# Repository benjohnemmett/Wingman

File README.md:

# Wingman
Hardware layout and code for a basic fixed wing flight controller.

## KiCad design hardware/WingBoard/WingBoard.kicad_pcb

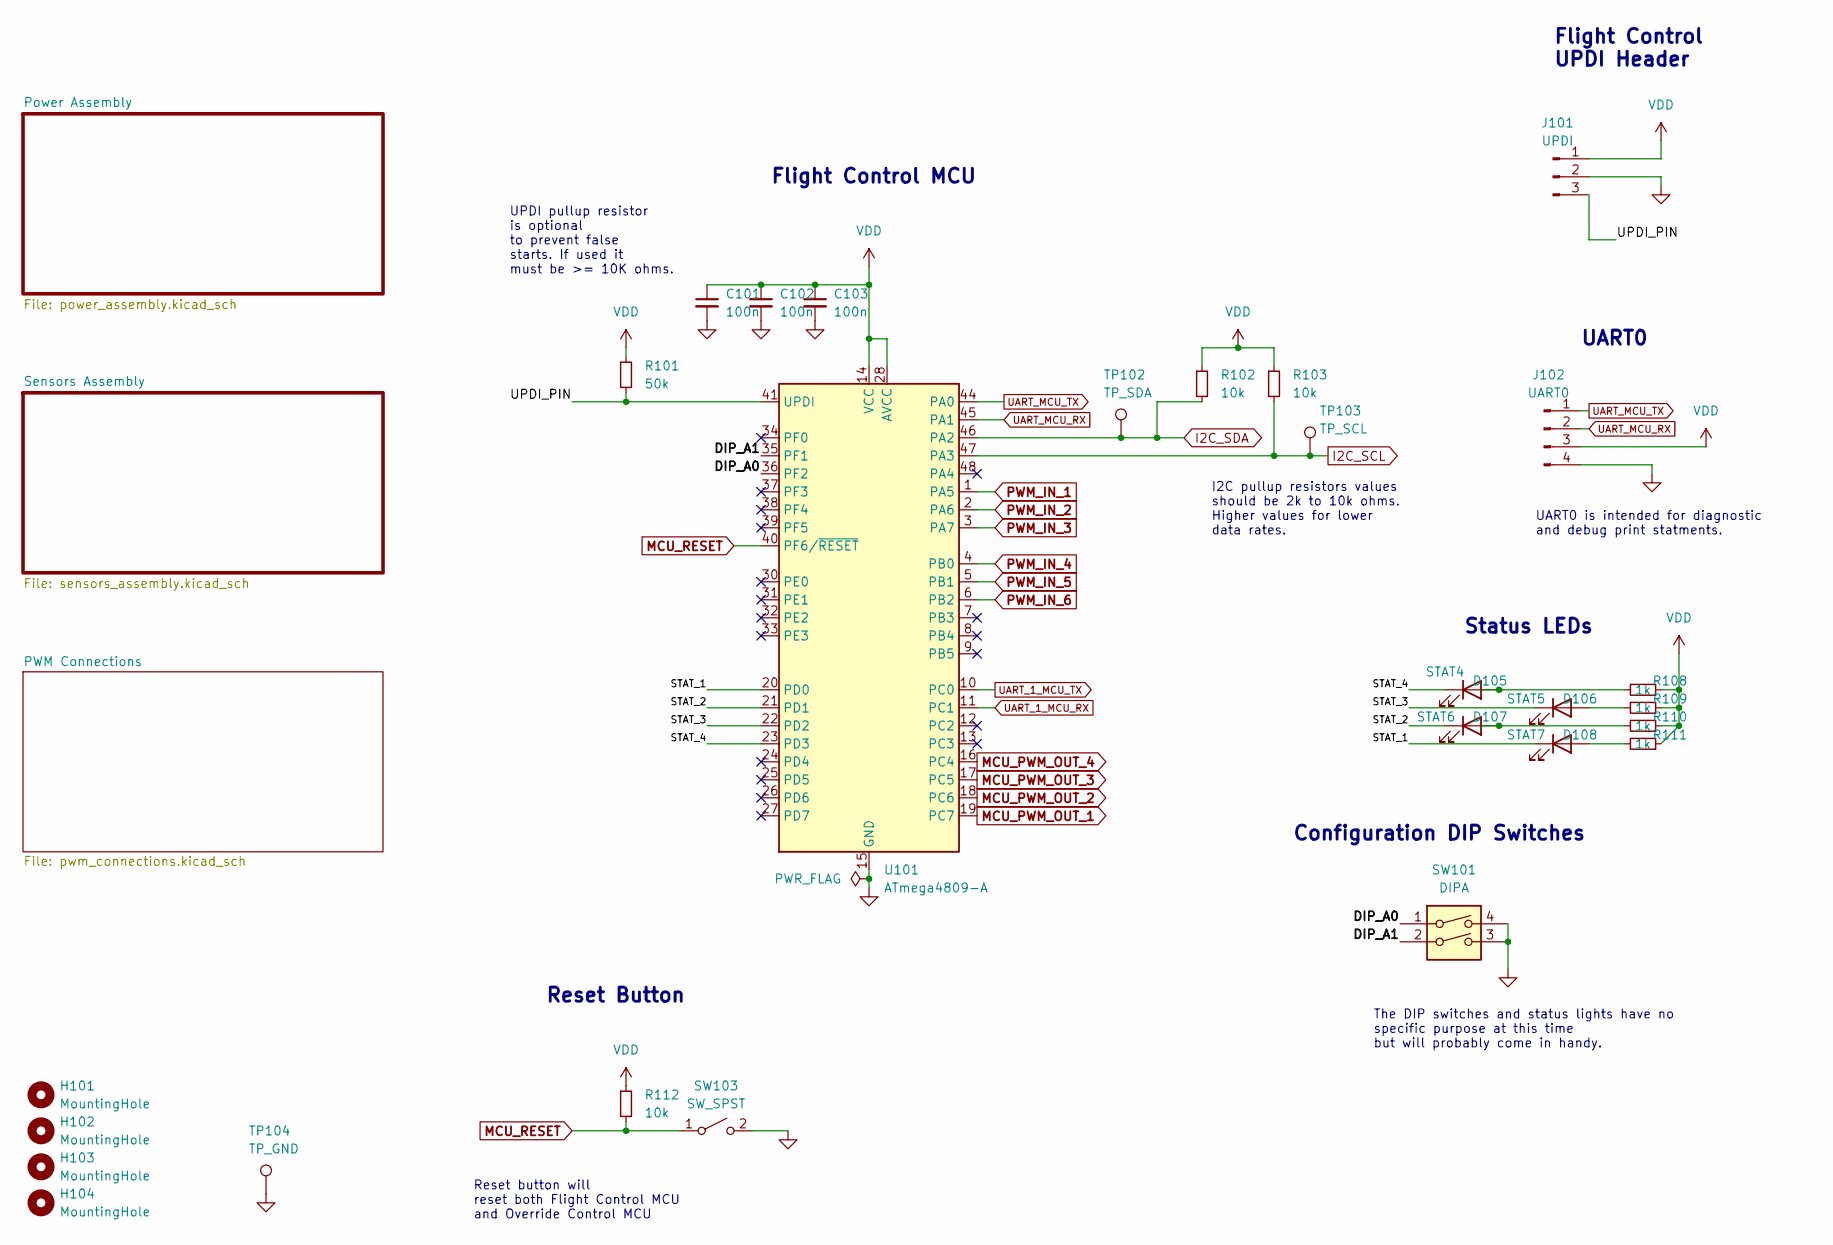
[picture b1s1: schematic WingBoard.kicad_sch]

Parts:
C101, C102, C103: 100n; C_0805_2012Metric_Pad1.18x1.45mm_HandSolder
D105: STAT4; LED_0805_2012Metric_Pad1.15x1.40mm_HandSolder
D106: STAT5; LED_0805_2012Metric_Pad1.15x1.40mm_HandSolder
D107: STAT6; LED_0805_2012Metric_Pad1.15x1.40mm_HandSolder
D108: STAT7; LED_0805_2012Metric_Pad1.15x1.40mm_HandSolder
H101, H102, H103, H104: MountingHole; MountingHole_3mm_Pad_Via
J101: UPDI; PinHeader_1x03_P2.54mm_Vertical
J102: UART0; PinHeader_1x04_P2.54mm_Vertical
R101: 50k; R_0805_2012Metric_Pad1.20x1.40mm_HandSolder
R102, R103, R112: 10k; R_0805_2012Metric_Pad1.20x1.40mm_HandSolder
R108, R109, R110, R111: 1k; R_0805_2012Metric_Pad1.20x1.40mm_HandSolder
SW101: DIPA; SW_DIP_SPSTx02_Slide_Copal_CHS-02B_W7.62mm_P1.27mm
SW103: SW_SPST; R-668127
TP102: TP_SDA; TestPoint_Pad_D1.5mm
TP103: TP_SCL; TestPoint_Pad_D1.5mm
TP104: TP_GND; TestPoint_Pad_D1.5mm
U101: ATmega4809-A; TQFP-48_7x7mm_P0.5mm

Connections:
/DIP_A0: SW101.1, U101.36 (PF2)
/DIP_A1: SW101.2, U101.35 (PF1)
/STAT_1: D108.1 (K), U101.20 (PD0)
/STAT_2: D107.1 (K), U101.21 (PD1)
/STAT_3: D106.1 (K), U101.22 (PD2)
/STAT_4: D105.1 (K), U101.23 (PD3)
/UPDI_PIN: J101.3, R101.2, U101.41 (UPDI)
GND: C101.2, C102.2, C103.2, J101.2, J102.4, SW101.3, SW101.4, SW103.2 (B), TP104.1, U101.15 (GND), U101.29 (GND), U101.43 (GND); also elsewhere on the board
I2C_SCL: R103.2, TP103.1, U101.47 (PA3); also elsewhere on the board
I2C_SDA: R102.2, TP102.1, U101.46 (PA2); also elsewhere on the board
MCU_PWM_OUT_1: U101.19 (PC7); also elsewhere on the board
MCU_PWM_OUT_2: U101.18 (PC6); also elsewhere on the board
MCU_PWM_OUT_3: U101.17 (PC5); also elsewhere on the board
MCU_PWM_OUT_4: U101.16 (PC4); also elsewhere on the board
MCU_RESET: R112.2, SW103.1 (A), U101.40 (PF6/~RESET); also elsewhere on the board
unnamed: D105.2 (A), R108.2
unnamed: D106.2 (A), R109.2
unnamed: D107.2 (A), R110.2
unnamed: D108.2 (A), R111.2
PWM_IN_1: U101.1 (PA5); also elsewhere on the board
PWM_IN_2: U101.2 (PA6); also elsewhere on the board
PWM_IN_3: U101.3 (PA7); also elsewhere on the board
PWM_IN_4: U101.4 (PB0); also elsewhere on the board
PWM_IN_5: U101.5 (PB1); also elsewhere on the board
PWM_IN_6: U101.6 (PB2); also elsewhere on the board
UART_1_MCU_RX: U101.11 (PC1); also elsewhere on the board
UART_1_MCU_TX: U101.10 (PC0); also elsewhere on the board
UART_MCU_RX: J102.2, U101.45 (PA1)
UART_MCU_TX: J102.1, U101.44 (PA0)
VDD: C101.1, C102.1, C103.1, J101.1, J102.3, R101.1, R102.1, R103.1, R108.1, R109.1, R110.1, R111.1, R112.1, U101.14 (VCC), U101.28 (AVCC), U101.42 (VCC); also elsewhere on the board

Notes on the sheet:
Configuration DIP Switches
Reset Button
Flight Control MCU
UPDI pullup resistor is optional to prevent false starts. If used it must be >= 10K ohms.
The DIP switches and status lights have no specific purpose at this time but will probably come in handy.
Reset button will reset both Flight Control MCU and Override Control MCU
Flight Control UPDI Header
Status LEDs
UART0 is intended for diagnostic and debug print statments.
I2C pullup resistors values should be 2k to 10k ohms. Higher values for lower data rates.
UART0

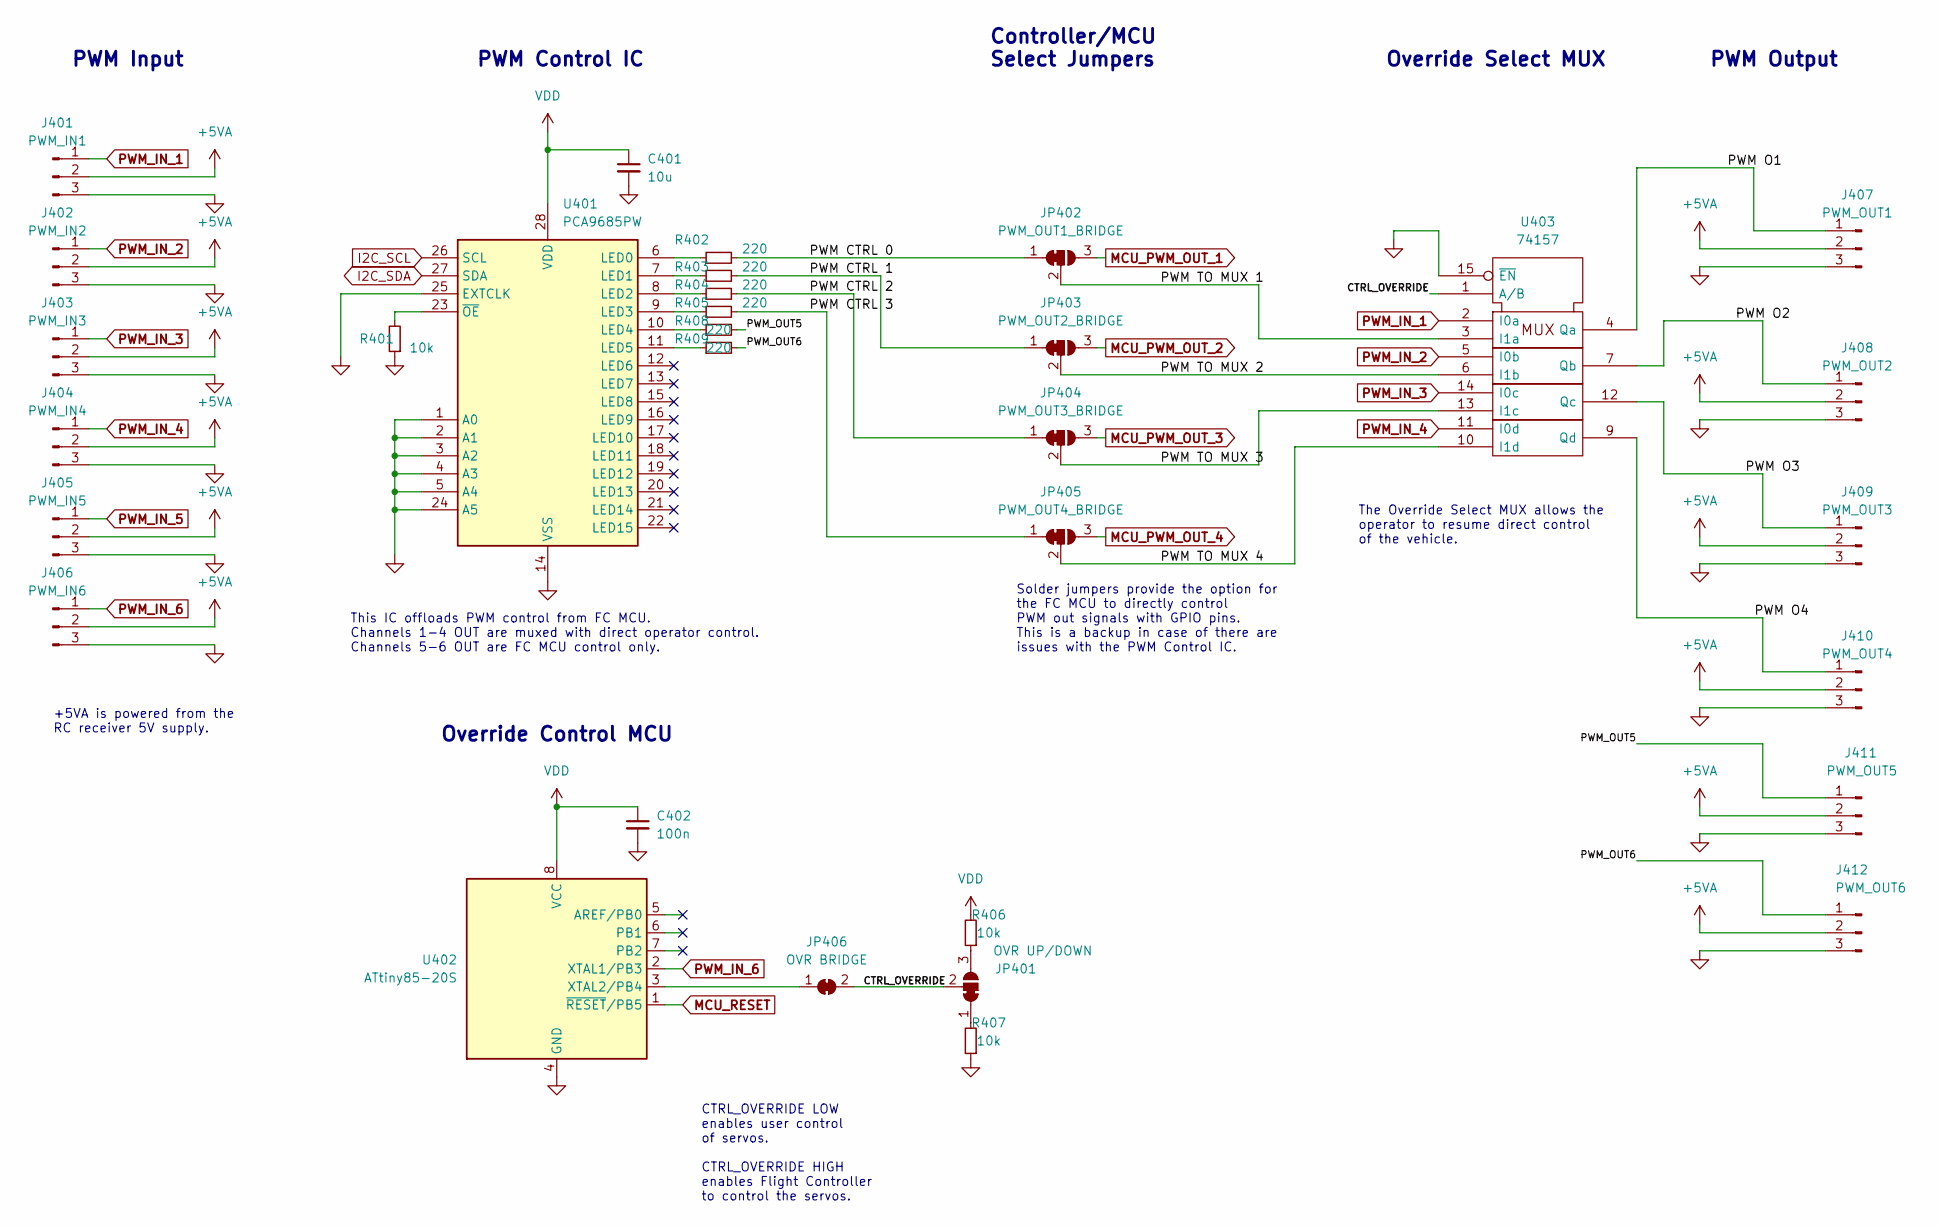
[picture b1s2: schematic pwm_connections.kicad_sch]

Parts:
C401: 10u; C_0805_2012Metric_Pad1.18x1.45mm_HandSolder
C402: 100n; C_0805_2012Metric_Pad1.18x1.45mm_HandSolder
J401: PWM_IN1; PinHeader_1x03_P2.54mm_Vertical
J402: PWM_IN2; PinHeader_1x03_P2.54mm_Vertical
J403: PWM_IN3; PinHeader_1x03_P2.54mm_Vertical
J404: PWM_IN4; PinHeader_1x03_P2.54mm_Vertical
J405: PWM_IN5; PinHeader_1x03_P2.54mm_Vertical
J406: PWM_IN6; PinHeader_1x03_P2.54mm_Vertical
J407: PWM_OUT1; PinHeader_1x03_P2.54mm_Vertical
J408: PWM_OUT2; PinHeader_1x03_P2.54mm_Vertical
J409: PWM_OUT3; PinHeader_1x03_P2.54mm_Vertical
J410: PWM_OUT4; PinHeader_1x03_P2.54mm_Vertical
J411: PWM_OUT5; PinHeader_1x03_P2.54mm_Vertical
J412: PWM_OUT6; PinHeader_1x03_P2.54mm_Vertical
JP401: OVR UP/DOWN; SolderJumper-3_P1.3mm_Bridged2Bar12_Pad1.0x1.5mm
JP402: PWM_OUT1_BRIDGE; SolderJumper-3_P1.3mm_Bridged12_Pad1.0x1.5mm
JP403: PWM_OUT2_BRIDGE; SolderJumper-3_P1.3mm_Bridged12_Pad1.0x1.5mm
JP404: PWM_OUT3_BRIDGE; SolderJumper-3_P1.3mm_Bridged12_Pad1.0x1.5mm
JP405: PWM_OUT4_BRIDGE; SolderJumper-3_P1.3mm_Bridged12_Pad1.0x1.5mm
JP406: OVR BRIDGE; SolderJumper-2_P1.3mm_Bridged2Bar_RoundedPad1.0x1.5mm
R401, R406, R407: 10k; R_0805_2012Metric_Pad1.20x1.40mm_HandSolder
R402, R403, R404, R405, R408, R409: 220; R_0805_2012Metric_Pad1.20x1.40mm_HandSolder
U401: PCA9685PW; TSSOP-28_4.4x9.7mm_P0.65mm
U402: ATtiny85-20S; SOIC-8W_5.3x5.3mm_P1.27mm
U403: 74157; SOP65P640X120-16N

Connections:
+5VA: J401.2, J402.2, J403.2, J404.2, J405.2, J406.2, J407.2, J408.2, J409.2, J410.2, J411.2, J412.2; also elsewhere on the board
/PWM Connections/CTRL_OVERRIDE: JP401.2 (C), JP406.2 (B), U403.1 (A/B)
/PWM Connections/PWM CTRL 0: JP402.1 (A), R402.2
/PWM Connections/PWM CTRL 1: JP403.1 (A), R403.2
/PWM Connections/PWM CTRL 2: JP404.1 (A), R404.2
/PWM Connections/PWM CTRL 3: JP405.1 (A), R405.2
/PWM Connections/PWM O1: J407.1, U403.4 (Qa)
/PWM Connections/PWM O2: J408.1, U403.7 (Qb)
/PWM Connections/PWM O3: J409.1, U403.12 (Qc)
/PWM Connections/PWM O4: J410.1, U403.9 (Qd)
/PWM Connections/PWM TO MUX 1: JP402.2 (C), U403.3 (I1a)
/PWM Connections/PWM TO MUX 2: JP403.2 (C), U403.6 (I1b)
/PWM Connections/PWM TO MUX 3: JP404.2 (C), U403.13 (I1c)
/PWM Connections/PWM TO MUX 4: JP405.2 (C), U403.10 (I1d)
/PWM Connections/PWM_OUT5: J411.1, R408.2
/PWM Connections/PWM_OUT6: J412.1, R409.2
GND: C401.2, C402.2, J401.3, J402.3, J403.3, J404.3, J405.3, J406.3, J407.3, J408.3, J409.3, J410.3, J411.3, J412.3, R401.1, R407.1, U401.1 (A0), U401.2 (A1), U401.3 (A2), U401.4 (A3), U401.5 (A4), U401.14 (VSS), U401.24 (A5), U401.25 (EXTCLK), U402.4 (GND), U403.8 (GND), U403.15 (~EN); also elsewhere on the board
I2C_SCL: U401.26 (SCL); also elsewhere on the board
I2C_SDA: U401.27 (SDA); also elsewhere on the board
MCU_PWM_OUT_1: JP402.3 (B); also elsewhere on the board
MCU_PWM_OUT_2: JP403.3 (B); also elsewhere on the board
MCU_PWM_OUT_3: JP404.3 (B); also elsewhere on the board
MCU_PWM_OUT_4: JP405.3 (B); also elsewhere on the board
MCU_RESET: U402.1 (~RESET/PB5); also elsewhere on the board
unnamed: JP401.1 (A), R407.2
unnamed: JP401.3 (B), R406.1
unnamed: JP406.1 (A), U402.3 (XTAL2/PB4)
unnamed: R401.2, U401.23 (~OE)
unnamed: R402.1, U401.6 (LED0)
unnamed: R403.1, U401.7 (LED1)
unnamed: R404.1, U401.8 (LED2)
unnamed: R405.1, U401.9 (LED3)
unnamed: R408.1, U401.10 (LED4)
unnamed: R409.1, U401.11 (LED5)
PWM_IN_1: J401.1, U403.2 (I0a); also elsewhere on the board
PWM_IN_2: J402.1, U403.5 (I0b); also elsewhere on the board
PWM_IN_3: J403.1, U403.14 (I0c); also elsewhere on the board
PWM_IN_4: J404.1, U403.11 (I0d); also elsewhere on the board
PWM_IN_5: J405.1; also elsewhere on the board
PWM_IN_6: J406.1, U402.2 (XTAL1/PB3); also elsewhere on the board
VDD: C401.1, C402.1, R406.2, U401.28 (VDD), U402.8 (VCC), U403.16 (VDD); also elsewhere on the board

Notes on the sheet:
+5VA is powered from the RC receiver 5V supply.
CTRL_OVERRIDE LOW enables user control of servos. CTRL_OVERRIDE HIGH enables Flight Controller to control the servos.
PWM Control IC
The Override Select MUX allows the operator to resume direct control of the vehicle.
PWM Input
PWM Output
Override Control MCU
Solder jumpers provide the option for the FC MCU to directly control PWM out signals with GPIO pins. This is a backup in case of there are issues with the PWM Control IC.
Controller/MCU Select Jumpers
This IC offloads PWM control from FC MCU. Channels 1-4 OUT are muxed with direct operator control. Channels 5-6 OUT are FC MCU control only.
Override Select MUX

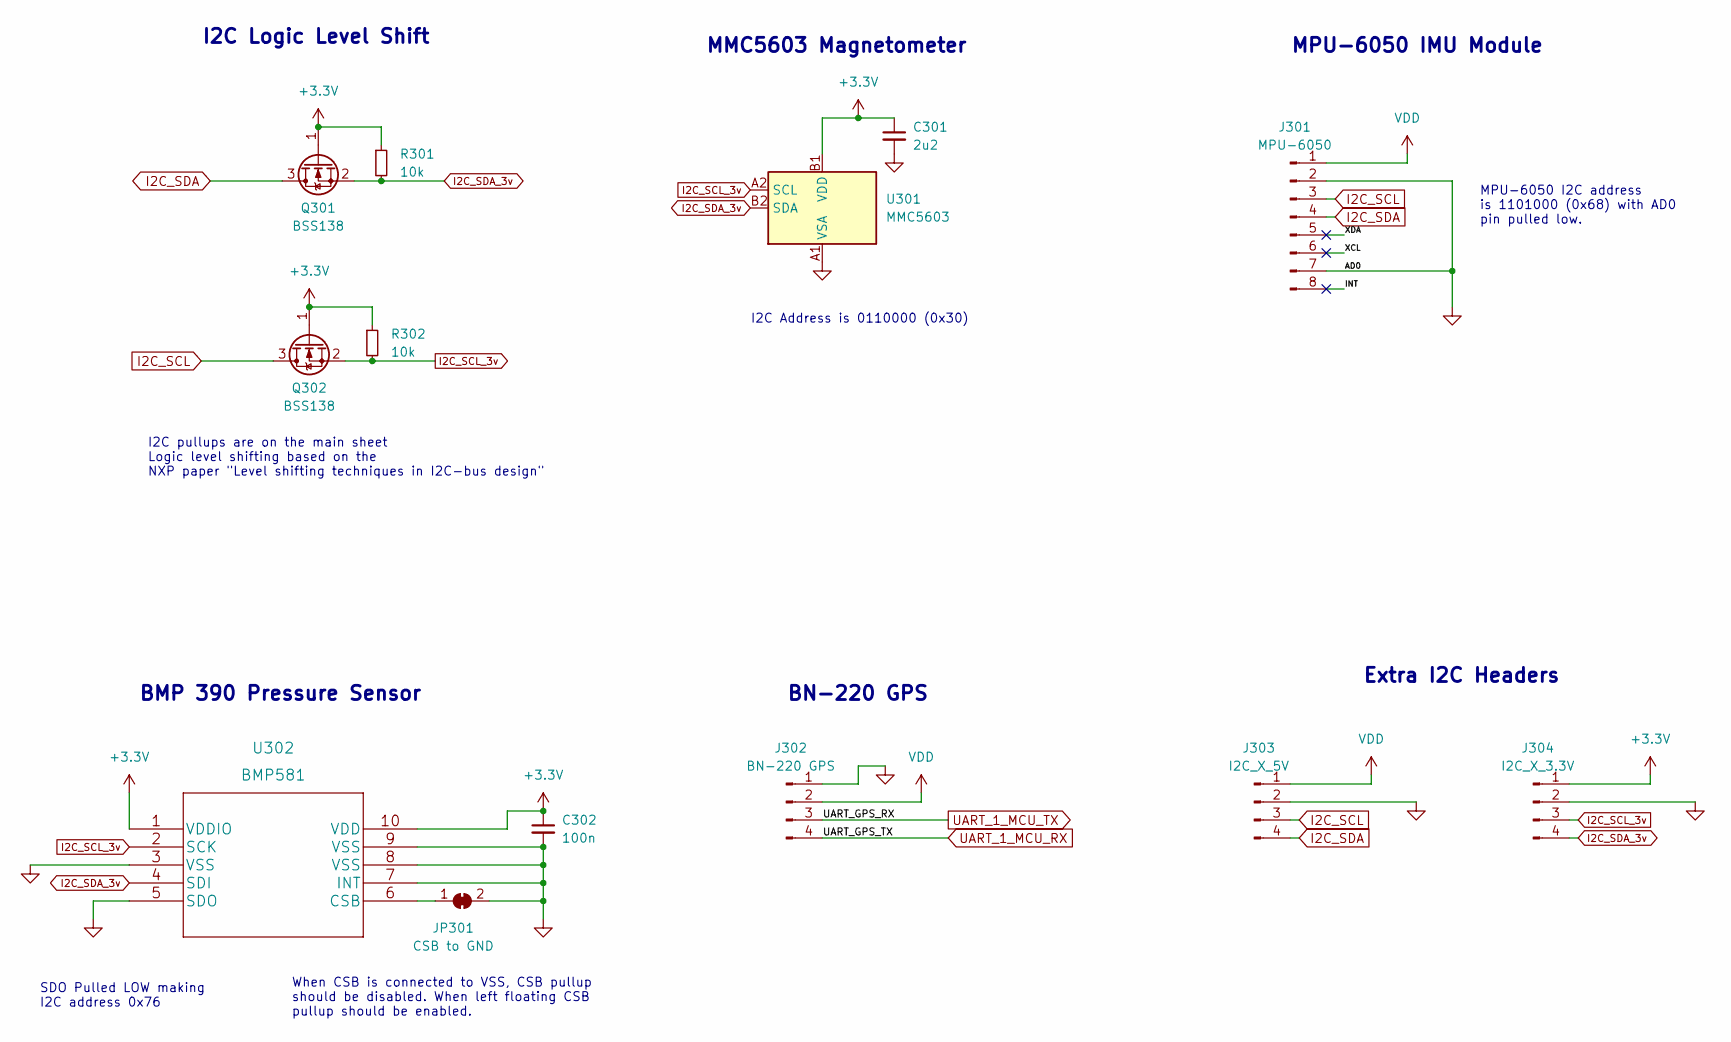
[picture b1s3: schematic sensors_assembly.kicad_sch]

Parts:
C301: 2u2; C_0805_2012Metric_Pad1.18x1.45mm_HandSolder
C302: 100n; C_0805_2012Metric_Pad1.18x1.45mm_HandSolder
J301: MPU-6050; PinHeader_1x08_P2.54mm_Vertical
J302: BN-220 GPS; JST_SH_BM04B-SRSS-TB_1x04-1MP_P1.00mm_Vertical
J303: I2C_X_5V; JST_SH_BM04B-SRSS-TB_1x04-1MP_P1.00mm_Vertical
J304: I2C_X_3.3V; JST_SH_BM04B-SRSS-TB_1x04-1MP_P1.00mm_Vertical
JP301: CSB to GND; SolderJumper-2_P1.3mm_Bridged_RoundedPad1.0x1.5mm
Q301, Q302: BSS138; SOT-23
R301, R302: 10k; R_0805_2012Metric_Pad1.20x1.40mm_HandSolder
U301: MMC5603; WLP-4_0.86x0.86mm_P0.4mm
U302: BMP581

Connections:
+3V3: C301.1, C302.1, J304.1, Q301.1 (G), Q302.1 (G), R301.1, R302.1, U301.B1 (VDD), U302.1 (VDDIO), U302.10 (VDD); also elsewhere on the board
/Sensors Assembly/INT: J301.8
/Sensors Assembly/XCL: J301.6
/Sensors Assembly/XDA: J301.5
GND: C301.2, C302.2, J301.2, J301.7, J302.1, J303.2, J304.2, JP301.2 (B), U301.A1 (VSA), U302.3 (VSS), U302.5 (SDO), U302.7 (INT), U302.8 (VSS), U302.9 (VSS); also elsewhere on the board
I2C_SCL: J301.3, J303.3, Q302.3 (D); also elsewhere on the board
I2C_SCL_3v: J304.3, Q302.2 (S), R302.2, U301.A2 (SCL), U302.2 (SCK)
I2C_SDA: J301.4, J303.4, Q301.3 (D); also elsewhere on the board
I2C_SDA_3v: J304.4, Q301.2 (S), R301.2, U301.B2 (SDA), U302.4 (SDI)
unnamed: JP301.1 (A), U302.6 (CSB)
UART_1_MCU_RX: J302.4; also elsewhere on the board
UART_1_MCU_TX: J302.3; also elsewhere on the board
VDD: J301.1, J302.2, J303.1; also elsewhere on the board

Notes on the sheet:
I2C pullups are on the main sheet Logic level shifting based on the NXP paper "Level shifting techniques in I2C-bus design"
BMP 390 Pressure Sensor
SDO Pulled LOW making I2C address 0x76
I2C Address is 0110000 (0x30)
MPU-6050 IMU Module
BN-220 GPS
Extra I2C Headers
MMC5603 Magnetometer
MPU-6050 I2C address is 1101000 (0x68) with AD0 pin pulled low.
When CSB is connected to VSS, CSB pullup should be disabled. When left floating CSB pullup should be enabled.
I2C Logic Level Shift

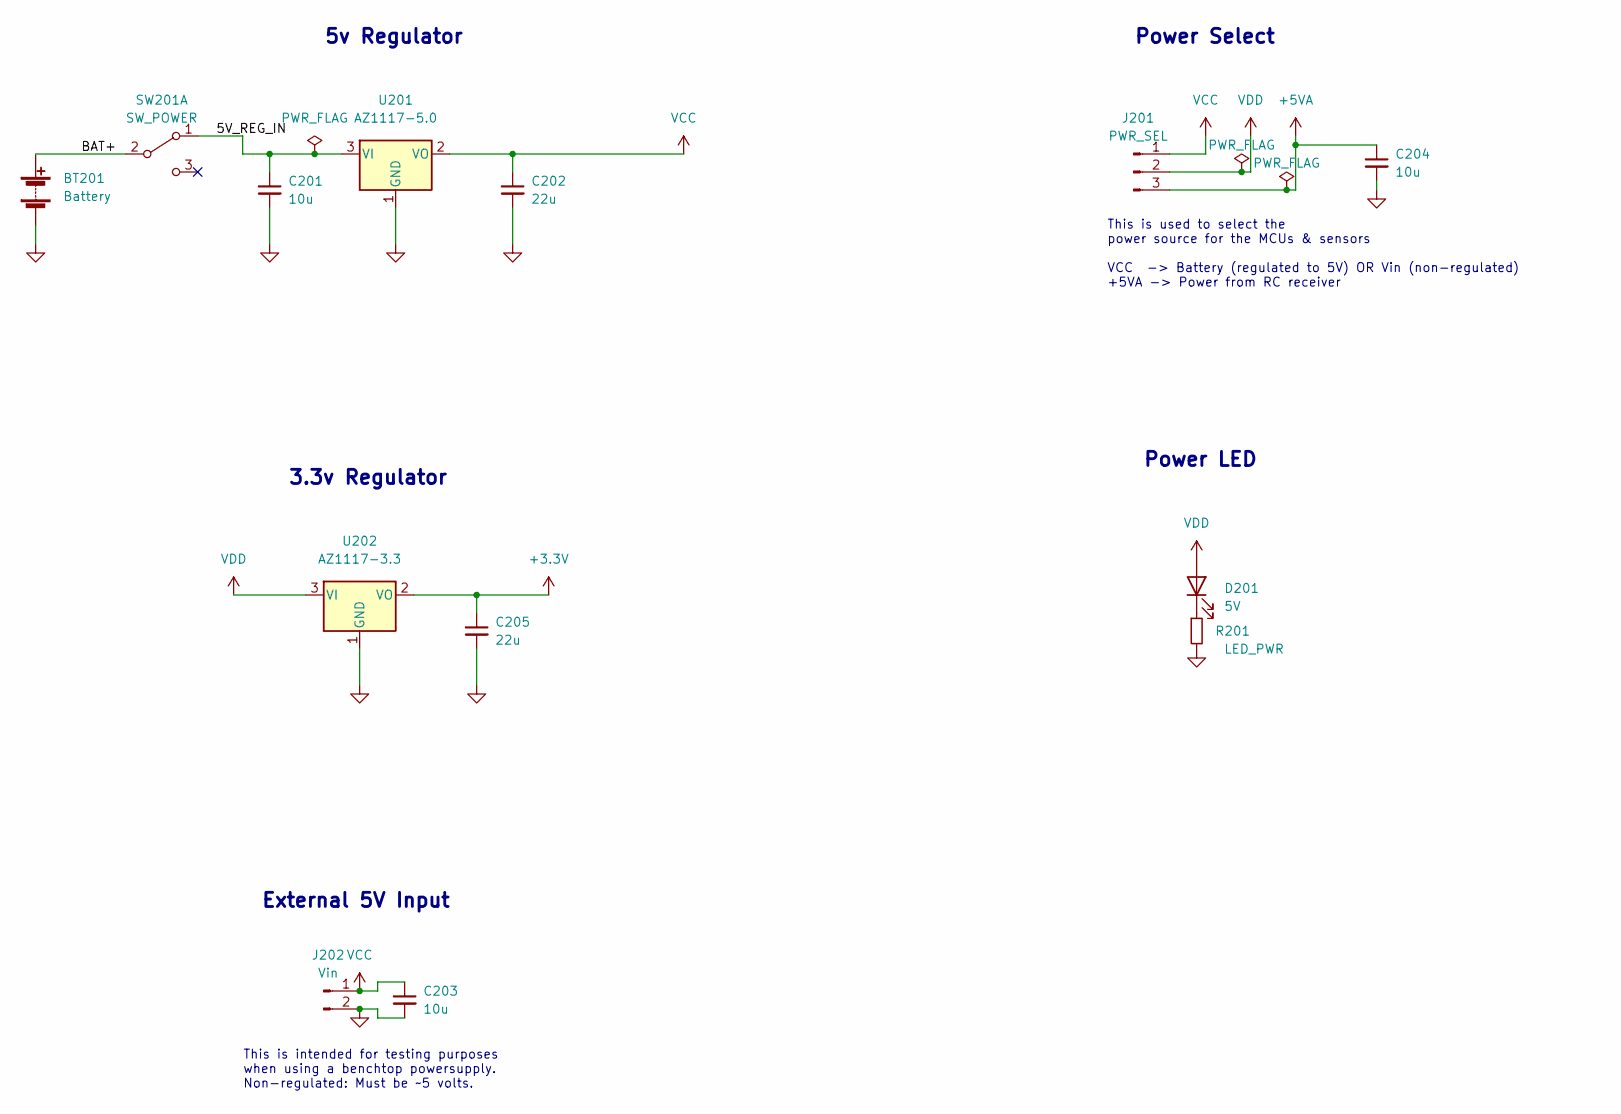
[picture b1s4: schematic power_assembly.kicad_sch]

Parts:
BT201: Battery; AMASS_XT30U-M_1x02_P5.0mm_Vertical
C201, C204: 10u; CP_Radial_D4.0mm_P1.50mm
C202, C205: 22u; CP_Radial_D4.0mm_P1.50mm
C203: 10u; C_0805_2012Metric_Pad1.18x1.45mm_HandSolder
D201: 5V; LED_0805_2012Metric_Pad1.15x1.40mm_HandSolder
J201: PWR_SEL; PinHeader_1x03_P2.54mm_Vertical
J202: Vin; PinHeader_1x02_P2.54mm_Vertical
R201: LED_PWR; R_0805_2012Metric_Pad1.20x1.40mm_HandSolder
SW201: SW_POWER; SW_DPDT_MSS22D18_6pin_bje
U201: AZ1117-5.0; AZ1117CH-5.0TRG1
U202: AZ1117-3.3; AZ1117CR-3.3TRG1

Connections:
+3V3: C205.1, U202.2 (VO); also elsewhere on the board
+5VA: C204.1, J201.3; also elsewhere on the board
/Power Assembly/5V_REG_IN: C201.1, SW201.1 (A), U201.3 (VI)
/Power Assembly/BAT+: BT201.1 (+), SW201.2 (B)
GND: BT201.2 (-), C201.2, C202.2, C203.2, C204.2, C205.2, J202.2, R201.2, U201.1 (GND), U202.1 (GND); also elsewhere on the board
unnamed: D201.1 (K), R201.1
VCC: C202.1, C203.1, J201.1, J202.1, U201.2 (VO)
VDD: D201.2 (A), J201.2, U202.3 (VI); also elsewhere on the board

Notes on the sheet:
This is intended for testing purposes when using a benchtop powersupply. Non-regulated: Must be ~5 volts.
5v Regulator
3.3v Regulator
Power LED
Power Select
External 5V Input
This is used to select the power source for the MCUs & sensors VCC -> Battery (regulated to 5V) OR Vin (non-regulated) +5VA -> Power from RC receiver

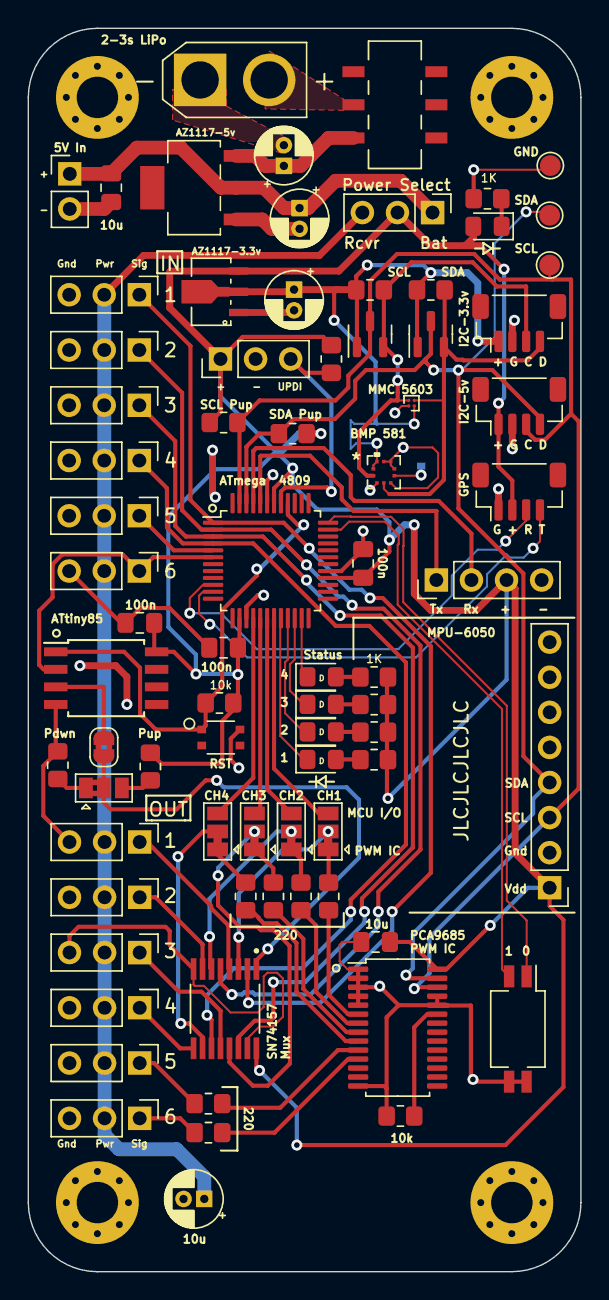
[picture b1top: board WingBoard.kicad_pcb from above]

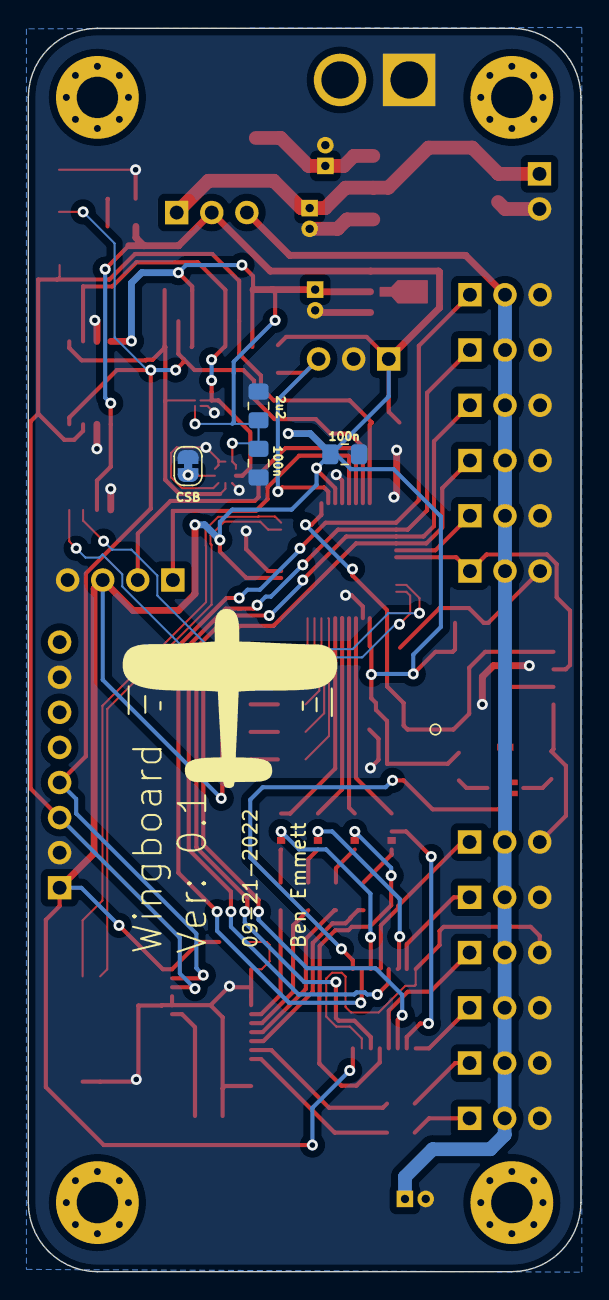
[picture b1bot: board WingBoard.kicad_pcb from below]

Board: 2 copper layers, 40.0 x 90.0 mm, 85 parts (4 on the bottom side), 64 nets.

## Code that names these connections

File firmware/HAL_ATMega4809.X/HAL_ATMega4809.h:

/* 
 * File:   HAL_ATMega4809.h
 * Author: ben
 *
 * Created on August 13, 2022, 12:28 PM
 */

#ifndef HAL_ATMEGA4809_H
#define	HAL_ATMEGA4809_H

#define F_CPU 20000000

#include <stdint.h>
#include <avr/io.h>
#include <util/delay.h>
#include <avr/interrupt.h>
#include "../Libraries/mcu-device-util/uart/uart.h"
#include "../HAL_Common.X/HAL_Functions.h"
#include "../HAL_Common.X/FlightControllerCommonTypes.h"
#include "../Libraries/mcu-device-util/PCA9685.X/PCA9685.h"

/* Peripheral Allocation
  TCA0  - PWM Servo CH 1-4 Output
  TCB0  - PWM CH 1 input
  TCB1  - PWM CH 2 input
  TCB2  - PWM CH 3 input
  TCB3  - PWM CH 4 input
  RTC   - 
  UART0 - 
  UART1 - 
  UART2 - 
  UART3 - 
  I2C   - MPU-6050/BMP-390/PCA9685
  SPI   - 
  ADC   - 
  GPIO D0 - STAT LED 1
  GPIO D1 - STAT LED 2
  GPIO D2 - STAT LED 3
  GPIO D3 - STAT LED 4
  GPIO F1 - DIP 1
  GPIO F2 - DIP 2
 * 
 * */

#define ROLL_CHANNEL 0
#define PITCH_CHANNEL 1
#define THROTTLE_CHANNEL 2
#define YAW_CHANNEL 3

#define PWM_IN_1_PORT A
#define PWM_IN_1_PIN 5
#define PWM_IN_1_PIN_bm (0x01 << PWM_IN_1_PIN)
#define PWM_IN_2_PORT A
#define PWM_IN_2_PIN 6
#define PWM_IN_2_PIN_bm (0x01 << PWM_IN_2_PIN)
#define PWM_IN_3_PORT A
#define PWM_IN_3_PIN 7
#define PWM_IN_3_PIN_bm (0x01 << PWM_IN_3_PIN)
#define PWM_IN_4_PORT B
#define PWM_IN_4_PIN 0
#define PWM_IN_4_PIN_bm (0x01 << PWM_IN_4_PIN)
#define PWM_IN_5_PORT B
#define PWM_IN_5_PIN 1
#define PWM_IN_5_PIN_bm (0x01 << PWM_IN_4_PIN)
#define PWM_IN_6_PORT B
#define PWM_IN_7_PIN 2
#define PWM_IN_8_PIN_bm (0x01 << PWM_IN_4_PIN)

#define PWM_OUT_1_PORT C
#define PWM_OUT_1_PIN 4
#define PWM_OUT_2_PORT C
#define PWM_OUT_2_PIN 5
#define PWM_OUT_3_PORT C
#define PWM_OUT_3_PIN 6
#define PWM_OUT_4_PORT C
#define PWM_OUT_4_PIN 7

#define STAT_LED_1_PORT D
#define STAT_LED_1_PIN 0
#define STAT_LED_2_PORT D
#define STAT_LED_2_PIN 1
#define STAT_LED_3_PORT D
#define STAT_LED_3_PIN 2
#define STAT_LED_4_PORT D
#define STAT_LED_4_PIN 3
#define STAT1_OFF() (PORTD.OUT |= (1 << STAT_LED_1_PIN))
#define STAT2_OFF() (PORTD.OUT |= (1 << STAT_LED_2_PIN))
#define STAT3_OFF() (PORTD.OUT |= (1 << STAT_LED_3_PIN))
#define STAT4_OFF() (PORTD.OUT |= (1 << STAT_LED_4_PIN))
#define STAT1_ON() PORTD.OUT &= ~(1 << STAT_LED_1_PIN)
#define STAT2_ON() PORTD.OUT &= ~(1 << STAT_LED_2_PIN)
#define STAT3_ON() PORTD.OUT &= ~(1 << STAT_LED_3_PIN)
#define STAT4_ON() PORTD.OUT &= ~(1 << STAT_LED_4_PIN)

#define DIP1_PORT F
#define DIP1_PIN 1
#define DIP2_PORT F
#define DIP2_PIN 2

#define BIT_VAL(pin) (0x01 << pin)

#define UART_TX_PORT A
#define UART_TX_PIN 0
#define UART_RX_PORT A
#define UART_RX_PIN 1

#ifdef	__cplusplus
extern "C" {
#endif


#ifdef	__cplusplus
}
#endif

#endif	/* HAL_ATMEGA4809_H */

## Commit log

2022-07-07 Add initial override controller code
2022-07-07 Initial override controller code
2022-07-07 Adding override controller makefile
2022-07-08 Add pct pwm range check, override hysteresis, and default pulse ready to 0
2022-07-08 0 pulse ready
2022-07-15 Adding FlightController MPLAB project
2022-07-17 Added more PID controller tests.
2022-07-28 Updated .gitignore
2022-07-28 Cleaned up pid controller & tests.
2022-08-09 Added integrator limits to the PID controller.
2022-08-09 Created ATMega4809 specific header.
2022-08-12 ATmega4809 clock configuration & blink test. Hardware test successful.
2022-08-14 ATMega4809 UART support added. Hardware test successful.
2022-08-15 Configured pin interrupts for PWM input capture pins. Tested & working.
2022-08-17 Configured 4-channel PWM input capture. Tested & working on ATMega4809.
2022-08-17 Moved OverrideController to firmware dir.
2022-08-18 Fixed issue to correct stored pulse width values.
2022-08-18 Cleaned up input capture ISR.
2022-08-23 Added PWM output logic. Tested & working.
2022-08-23 Updated to make PWM output more accurate.
2022-08-26 Running passthrough test. Appears to be working, not thoroughly tested yet.
2022-08-28 Passthrough improved. Tested on RC plane elevator + rudder, working.
2022-09-07 Moved atmega4809 UART code to separate library.
2022-09-08 Schematic design started.
2022-09-08 Added extra I2C headers to the schematic.
2022-09-08 Added pwm controller.
2022-09-09 Hardware update: status LEDs, DIP switches, & test points.
2022-09-10 Minor hardware design updates and assigned PCB footprints
2022-09-11 PCB rough layout done.
2022-09-19 Hardware layout v0.1 complete.
2022-09-21 Final wingboard v0.1 hardware design.
2022-10-09 Added code to test status LEDs on startup.
2022-10-11 Reading DIP switches.
2023-07-03 Added PID reset function.
2023-07-03 Added PID integrator bounds tests.
2023-07-05 Added unit tests for PID controller for dt != 1.0
2023-07-07 Added simple python wrapper to test PID library.
2023-07-10 Added new firmware project, FlightLogger.
2023-07-23 Created new projects for HAL interface definitions & ATMega4809 implementation to share between projects.
2023-07-27 renamed HAL functions to HAL_
2023-07-31 Logger is writing acceleration data.
2023-08-01 Pulled in MPU-6050 updates from submodule & updated flight logger to write gyro data.
2024-01-15 FlightLogger print cleanup.
2024-01-16 Added pressure & temp to FlightLogger.
2024-02-15 WIP: Working on PID controller tests
2024-02-16 FlightLogger logs PWM in 1-4.
2024-06-23 Updated to use mcu-device-util library
2024-09-21 Updated override controller pin change interrupt.
2024-09-25 WIP: Basic Flight Control Logic.
2024-09-25 Updating submodule ref
2024-09-25 Adding missing MPLAB X IDE netbeans project files.
2024-09-25 Status LED 4 toggles on each update loop iteration.

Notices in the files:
parts and their libraries:
Copyright 2021 Accelerated Designs. All rights reserved.
